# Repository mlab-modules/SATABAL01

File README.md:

# SATABAL01 - passive coax to SATA balun module 

SATABAL01 is a passive RF balun module designed to interface high-speed differential pairs used in SATA data lines with unbalanced coaxial transmission lines. This module is primarily intended for applications requiring measurement, testing, or signal routing of SATA signals over RF-grade coaxial cables.

## Features

- Converts differential SATA signals to unbalanced RF signals and vice versa
- Suitable for signal bandwidths from 4.5 MHz to 3000 MHz
- Dual-channel design for full SATA differential pair
- Standard SATA connector (J1)
- MCX or SMA coaxial connectors (J2, J3)
- Uses Mini-Circuits TC1-1-13MX+ wideband RF balun transformers
- Compact design suitable for integration into test setups or embedded systems

## Functional Description

The module contains two identical wideband RF balun transformers (Mini-Circuits TC1-1-13MX+), each used to convert one differential signal pair to a single-ended signal. The SATA connector (J1) provides two differential pairs. Each pair is routed through a balun (T1, T2), with the single-ended outputs available at connectors J3 and J2 respectively. These connectors support either MCX or SMA types depending on user preference.

## Electrical Specifications (Per Channel)

Based on the TC1-1-13MX+ balun:

- **Impedance Ratio**: 1:1  
- **Frequency Range**: 4.5 MHz to 3000 MHz  
- **Insertion Loss**:  
  - 4.5–1000 MHz: typ. 1.0 dB  
  - 1000–2000 MHz: typ. 2.0 dB  
  - 2000–3000 MHz: typ. 3.0 dB  
- **Amplitude Unbalance**: typ. 0.5 dB (up to 2000 MHz)  
- **Phase Unbalance**: typ. 2–3 degrees (up to 2000 MHz)  

> Refer to the [TC1-1-13MX+ datasheet](https://www.minicircuits.com/pdfs/TC1-1-13MX+.pdf) for detailed transformer characteristics【7†source】.

## Schematic Overview

- **J1**: SATA 7-pin connector (AMP 67491-1030)
- **T1, T2**: Mini-Circuits TC1-1-13MX+ transformers for each differential pair
- **J2, J3**: Output via MCX/SMA connectors
- **H1–H4**: Mounting pads and ground.

## Typical Use Cases

- Probing SATA lines with RF measurement equipment
- High-frequency signal transmission over coaxial cable
- Balancing/unbalancing of high-speed digital signals and clock

## Assembly Notes

- Ensure correct orientation of baluns as per datasheet marking.
- Match connector types (MCX or SMA) to your coaxial cabling needs.
- Use controlled impedance traces for differential signal integrity.

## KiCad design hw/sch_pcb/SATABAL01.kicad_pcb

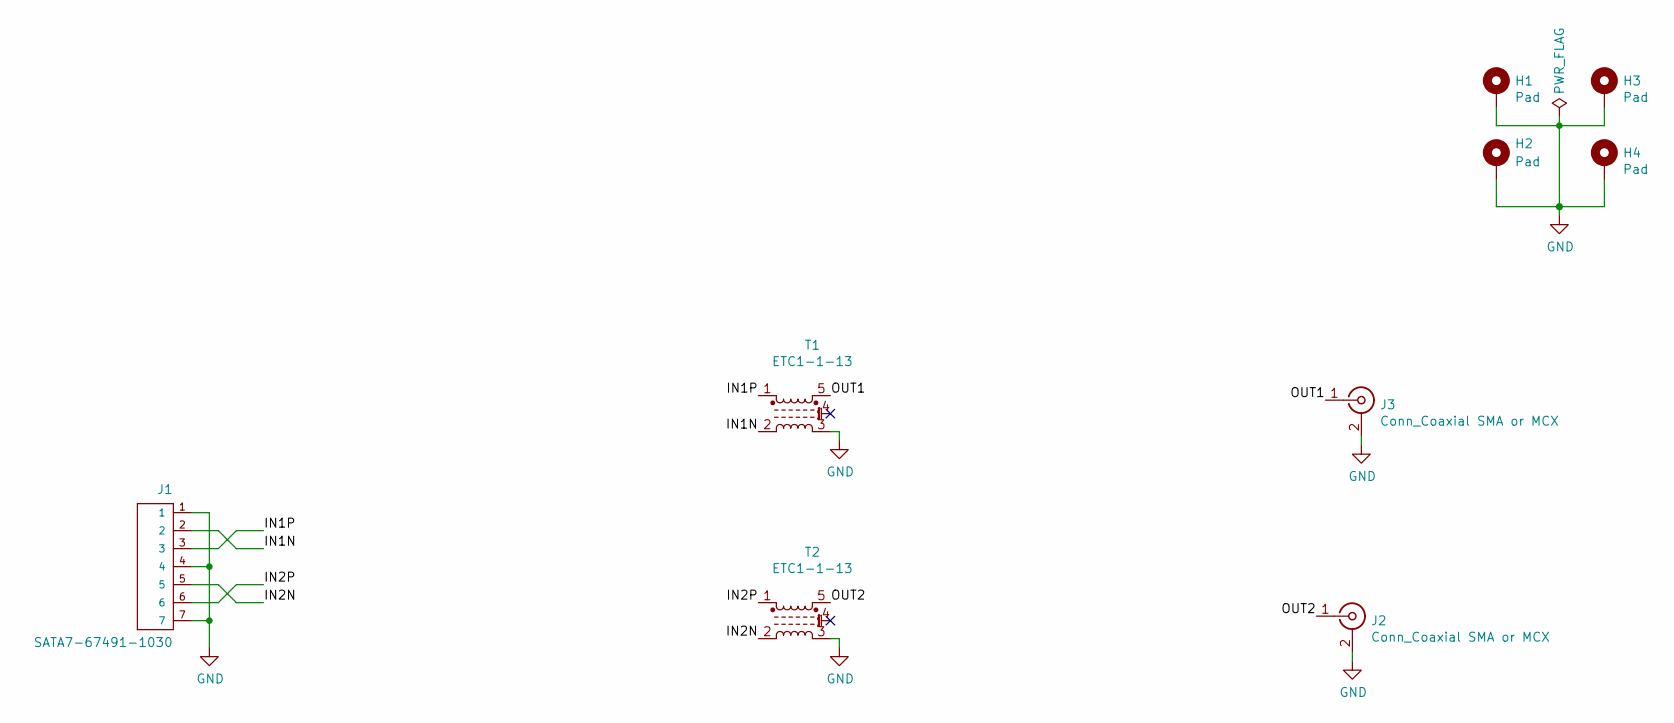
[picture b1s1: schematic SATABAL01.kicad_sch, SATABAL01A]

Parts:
H1, H2, H3, H4: Pad; MountingHole_3mm
J1: SATA7-67491-1030; SATA-7_THT_VERT_2
J2, J3: Conn_Coaxial SMA or MCX; SMA_Amphenol_901-144_Vertical
T1, T2: ETC1-1-13; Transformer_MACOM_SM-22

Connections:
/IN1N: J1.2, T1.2
/IN1P: J1.3, T1.1
/IN2N: J1.5, T2.2
/IN2P: J1.6, T2.1
/OUT1: J3.1 (In), T1.5
/OUT2: J2.1 (In), T2.5
GND: H1.1, H2.1, H3.1, H4.1, J1.1, J1.4, J1.7, J1.8 (4), J1.9 (7), J2.2 (Ext), J3.2 (Ext), T1.3, T2.3

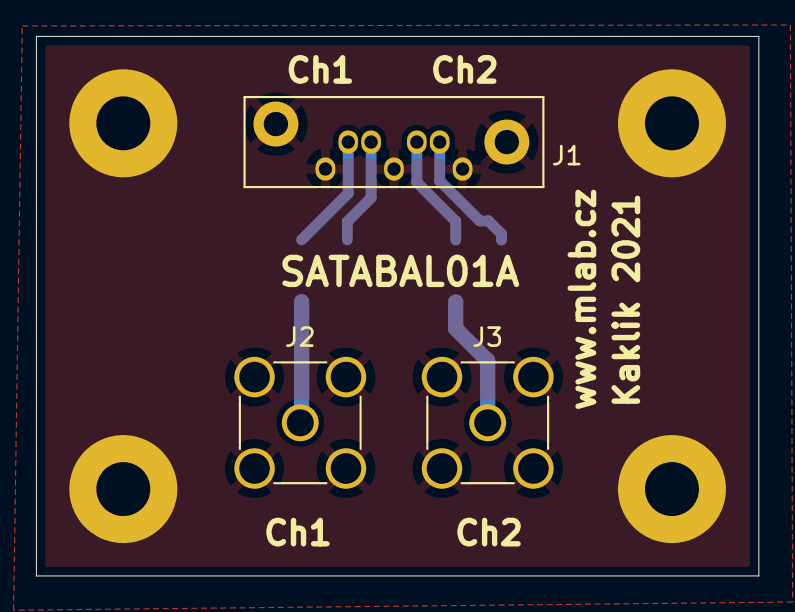
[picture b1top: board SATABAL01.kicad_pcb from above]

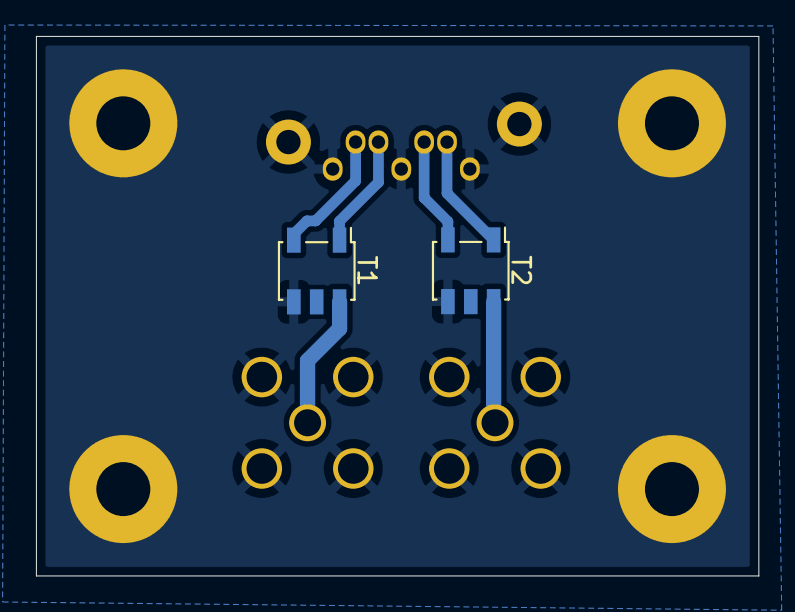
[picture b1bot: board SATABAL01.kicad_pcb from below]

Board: 2 copper layers, 40.1 x 30.0 mm, 9 parts (2 on the bottom side), 7 nets.

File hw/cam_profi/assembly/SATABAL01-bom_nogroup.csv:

Component,Description,Part,References,Value,Footprint,Quantity Per PCB,Datasheet,ust_id
1,"coaxial connector (BNC, SMA, SMB, SMC, Cinch/RCA, LEMO, ...)",Conn_Coaxial,J2J3,Conn_Coaxial SMA or MCX,SMA_Amphenol_901-144_Vertical,2,~,5c70984412875079b91f87ac
2,,SATA7-67491-1030-konektory,J1,SATA7-67491-1030,SATA-7_THT_VERT_2,1,,5c70984712875079b91f8a7b
3,"4.5-4000MHz 1:1 RF Transformer, Balanced Transmission Line, SM-22",ETC1-1-13,T1T2,ETC1-1-13,Transformer_MACOM_SM-22,2,https://www.minicircuits.com/pdfs/TC1-1-13MX+.pdf,5face38612875025b3977e95

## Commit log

2021-04-28 Balun schematics WIP.
2021-04-29 PCB layout WIP.
2021-04-30 Fix issue in ground connection.
2021-05-03 Layout improvement Add module metadata.
2021-05-16 Improve silkscreen.
2021-05-17 Minor silkscreen and layout improvements.
2021-05-17 Add tranformer datasheet and PDF schematics export.
2021-05-18 Generování výrobních dat
2021-05-18 Edit data
2021-05-18 Rename KICAD project
2021-05-18 Edit production data
2021-05-18 výrobní data
2021-06-07 Add mathing UST_ID to components. #1
2021-06-08 Generate BOM
2021-06-25 Add a photo of module.
2022-04-06 automated commit; add github actions
2022-04-06 Update actions products
2023-05-25 Update metadata files
2023-05-28 Update workflow files
2023-07-05 automated commit; rename source files to new naming convence
2023-09-16 Update image to image_title
2023-09-16 Update status
2025-12-20 Update to KiCADv9.
2025-12-20 Fix ERC error.
2025-12-20 Update symbols from libraries.
2025-12-20 Rectangle outline converted to lines.
2025-12-20 Generate meaningful readme.
